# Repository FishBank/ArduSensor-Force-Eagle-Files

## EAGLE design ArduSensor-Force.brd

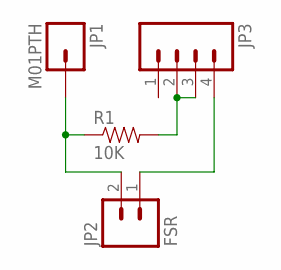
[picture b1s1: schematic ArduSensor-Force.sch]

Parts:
JP1: M01PTH; 1X01
JP2: FSR; 1X02
JP3: M04PTH; 1X04
R1: 10K; AXIAL-0.3

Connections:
unnamed: JP1.1, JP2.2, R1.P$1 (1)
unnamed: JP3.2, JP3.3, R1.P$2 (2)
unnamed: JP2.1, JP3.4

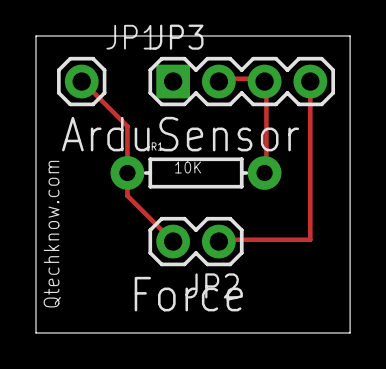
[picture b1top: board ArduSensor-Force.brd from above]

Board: 2 copper layers, 17.5 x 16.5 mm, 4 parts (0 on the bottom side), 3 nets.

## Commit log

2012-07-13 Schematic

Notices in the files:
parts and their libraries:
SFE Connectors: Licensing: CC v3.0 Share-Alike You are welcome to use this library for commercial purposes.
